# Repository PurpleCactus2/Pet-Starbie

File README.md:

# Starbie
A motion controlled PCB pet!

### Introduction
This is Starbie, a motion controlled, Tamagotchi style digital pet meant to keep you company on your desk. It uses a microcontroller, motion and enviroment sensor, along with 2 buttons to allow you to interact with it. It was made with the help of this wonderful [guide](https://github.com/SharKingStudios/Starbie/tree/main) by Logan Peterson which guided me through the entire process of making my first PCB.

Its main functions include:
- A stats screen for your pet
- Nap, Play and Pet actions
- A shake interaction

And you can also customise your own sprite!

However, I have also added a couple of my own features:
- A basic power LED indicating when starbie is on
- An external battery circuit making starbie portable
- A 3D printed enclosure to tie everything together

### PCB and Schematic
This is the entire schematic using the connections and components that are described in the guide.
The ESP32-C3 connects the buttons through 2 GPIO pins, the screen and the motion sensor through I2C, and also supplies the steady 3.3V that the circuit needs.

<br>
<br>
Here are the 2 things that I added:
<br>
<br>
This is the basic power LED which connects to the 3.3V output of the ESP32-C3 through a 220Ω resistor. The LED itself will just be a standard 5mm 2V red LED that indicates whenever the circuit is connected to power.
<br>

<br>
<br>
This is the external battery circuit that will power starbie through a battery. It will use a 500mAh 3.7V 503035 liPo that connects straight to the battery pads on the underside of the Xiao, meaning it will be charged and regulated with the battery charger already integrated into the microcontroller. A switch has also been included in line from the battery so that starbie can be turned off easily.
<br>

<br>
<br>
PCB:
<br>
<br>
Here, I have used a similar layout and shape as shown in the guide. <br> <br>
At first, I tried experimenting with the positioning of the buttons by having them side by side, but this turned out to make to routing more complicated by requiring more traces on the bottom layer. Because of this, I decided to align the buttons vertically, even if it is a little more inconvenient. I have also added a couple of M3 screw holes on the edges so that I can mount the PCB in the enclosure that I designed.

<br>
<br>
Here are the contacts for the battery pads of the Xiao:

These pads won't actually be making contact with the pads on the Xiao, since it will be raised on top of header pins. But, I have put through-holes on these pads to allow for header pins to be pushed through them. This should allow the battery to be soldered directly to these pins from the bottom, making managing space a lot easier.

### Code
Most of the code is from the preset given by the guide, but there are some parts which I have modified:
<br>
<br>
These 2 pins were previously mismatched with SCL on 7 and SDA on 6 while my PCB and schematic has SCL on 6 and SDA on 7. This would have thrown an error where the Xiao would not be able to communicate with the screen or motion sensor. Luckily the ESP32-C3 is able to reroute these I2C connections easily.
~~~cpp
const int I2C_SDA_PIN = 7;
const int I2C_SCL_PIN = 6;
~~~
<br>
<br>
This was an optional function given in the guide that could be inserted above the drawHeart function. It will create sparkles behind the pet as it moves.

~~~cpp
void drawSparkle(int x, int y) {
  display.drawPixel(x, y - 2, SSD1306_WHITE);
  display.drawPixel(x - 1, y - 1, SSD1306_WHITE);
  display.drawPixel(x + 1, y - 1, SSD1306_WHITE);
  display.drawPixel(x - 2, y, SSD1306_WHITE);
  display.drawPixel(x, y, SSD1306_WHITE);
  display.drawPixel(x + 2, y, SSD1306_WHITE);
  display.drawPixel(x - 1, y + 1, SSD1306_WHITE);
  display.drawPixel(x + 1, y + 1, SSD1306_WHITE);
  display.drawPixel(x, y + 2, SSD1306_WHITE);
}
~~~

This is what actually calls the drawSparkle function
~~~cpp
if (!isNapping() && (now / 250) % 2 == 0) {
  drawSparkle(petX - 4, petY + 18);
}
~~~
<br>
<br>
This is a byte list created from a custom 32x32px sprite which I drew.

~~~cpp
const uint8_t PROGMEM PET_SPRITE[] = {
  0x00, 0x0f, 0xf0, 0x00, 0x00, 0x70, 0x0e, 0x00, 0x01, 0x80, 0x01, 0x80, 0x02, 0x00, 0x00, 0x40, 
	0x04, 0x00, 0x00, 0x20, 0x08, 0x00, 0x00, 0x10, 0x10, 0x00, 0x00, 0x08, 0x20, 0x00, 0x38, 0x04, 
	0x20, 0x00, 0x38, 0x04, 0x40, 0x00, 0x30, 0x02, 0x40, 0x00, 0x00, 0x02, 0x40, 0x00, 0x00, 0x02, 
	0x80, 0x00, 0x00, 0x3c, 0x80, 0x00, 0x03, 0xe0, 0x80, 0x00, 0x1e, 0x00, 0x80, 0x00, 0x20, 0x00, 
	0x80, 0x00, 0x20, 0x00, 0x80, 0x00, 0x1e, 0x00, 0x80, 0x00, 0x03, 0xe0, 0x80, 0x00, 0x00, 0x3c, 
	0x40, 0x00, 0x00, 0x02, 0x40, 0x00, 0x00, 0x02, 0x40, 0x00, 0x00, 0x02, 0x20, 0x00, 0x00, 0x04, 
	0x20, 0x00, 0x00, 0x04, 0x10, 0x00, 0x00, 0x08, 0x08, 0x00, 0x00, 0x10, 0x04, 0x00, 0x00, 0x20, 
	0x02, 0x00, 0x00, 0x40, 0x01, 0x80, 0x01, 0x80, 0x00, 0x70, 0x0e, 0x00, 0x00, 0x0f, 0xf0, 0x00,
};
~~~

The sprite should look like this:

### Enclosure
I wanted to make the PCB a little more personalised and I also wanted to have a neat place to store the battery. Because of this, I decided to design a 3D printable enclosure meant to be assembled with screws and a little bit of glue.

This is the enclosure as a whole. It has several holes on the top for each component that sticks through, along with 4 M2.5x8 screw holes along the edge of the lid for assembly.

<br>
<br>
<br>
This is how the battery and the switch are arranged below the PCB. The battery is completely hidden inside the bottom of the case while the switch sticks out a little bit through a hole so that you can use it.

<br>
<br>
<br>
This is how the entire enclosure is assembled. The battery and the PCB are inserted into the case first, along with 4 M3x8 that screw into holes in the bottom of the case. The lid is then put on with 4 M2.5x8 along its edges. Finally after trimming the pins of the switch, it is super-glued onto the back of the PCB next to the battery.

<br>
<br>
<br>
Here is a more detailed view of the screw holes inside the case as well as of the battery and switch placement:

### BOM
| Part | What it's for | Qty | Unit | Total | Vendor | Expected Discounted Price (At time last checked) |
| --- | --- | --- | --- | --- | --- | --- |
| [XIAO ESP32 C3](https://www.aliexpress.com/item/1005008791937363.html?spm=a2g0o.productlist.main.57.73cf3205oRycWV&algo_pvid=b26d9f0b-0926-4227-8f6e-a914df534036&algo_exp_id=b26d9f0b-0926-4227-8f6e-a914df534036-54&pdp_ext_f=%7B%22order%22%3A%221488%22%2C%22spu_best_type%22%3A%22price%22%2C%22eval%22%3A%221%22%2C%22fromPage%22%3A%22search%22%7D&pdp_npi=6%40dis%21NOK%2183.14%2110.88%21%21%218.33%211.09%21%402103810f17916626052361400e0f0b%2112000052930246748%21sea%21NO%218463637778%21X%211%210%21n_tag%3A-29911%3Bd%3A22d43e35%3Bm03_new_user%3A-29895%3BpisId%3A5000000219435413&curPageLogUid=9fTnC7rBXexc&utparam-url=scene%3Asearch%7Cquery_from%3A%7Cx_object_id%3A1005008791937363%7C_p_origin_prod%3A) | The main microcontroller | 1 | $8.84 | $8.84 | [AliExpress](https://www.aliexpress.com/item/1005008791937363.html?spm=a2g0o.productlist.main.57.73cf3205oRycWV&algo_pvid=b26d9f0b-0926-4227-8f6e-a914df534036&algo_exp_id=b26d9f0b-0926-4227-8f6e-a914df534036-54&pdp_ext_f=%7B%22order%22%3A%221488%22%2C%22spu_best_type%22%3A%22price%22%2C%22eval%22%3A%221%22%2C%22fromPage%22%3A%22search%22%7D&pdp_npi=6%40dis%21NOK%2183.14%2110.88%21%21%218.33%211.09%21%402103810f17916626052361400e0f0b%2112000052930246748%21sea%21NO%218463637778%21X%211%210%21n_tag%3A-29911%3Bd%3A22d43e35%3Bm03_new_user%3A-29895%3BpisId%3A5000000219435413&curPageLogUid=9fTnC7rBXexc&utparam-url=scene%3Asearch%7Cquery_from%3A%7Cx_object_id%3A1005008791937363%7C_p_origin_prod%3A) | $2.46 |
| [0.96" OLED](https://www.aliexpress.com/item/1005006141235306.html?spm=a2g0o.productlist.main.1.4f9d12780KL1MO&algo_pvid=39c5fa34-e376-41e0-8849-d3f33eab2a7b&algo_exp_id=39c5fa34-e376-41e0-8849-d3f33eab2a7b-0&pdp_ext_f=%7B%22order%22%3A%2226478%22%2C%22spu_best_type%22%3A%22price%22%2C%22eval%22%3A%221%22%2C%22fromPage%22%3A%22search%22%7D&pdp_npi=6%40dis%21NOK%2122.70%2122.70%21%21%2115.22%2115.22%21%400b5e1a3817916636389462446e0d42%2112000035944225406%21sea%21NO%218463637778%21X%211%210%21n_tag%3A-29911%3Bd%3A22d43e35%3Bm03_new_user%3A-29895&curPageLogUid=3zuT5PcCui5q&utparam-url=scene%3Asearch%7Cquery_from%3A%7Cx_object_id%3A1005006141235306%7C_p_origin_prod%3A) | For displaying the sprite and actions | 1 | $2.31 | $2.31 | [AliExpress](https://www.aliexpress.com/item/1005006141235306.html?spm=a2g0o.productlist.main.1.4f9d12780KL1MO&algo_pvid=39c5fa34-e376-41e0-8849-d3f33eab2a7b&algo_exp_id=39c5fa34-e376-41e0-8849-d3f33eab2a7b-0&pdp_ext_f=%7B%22order%22%3A%2226478%22%2C%22spu_best_type%22%3A%22price%22%2C%22eval%22%3A%221%22%2C%22fromPage%22%3A%22search%22%7D&pdp_npi=6%40dis%21NOK%2122.70%2122.70%21%21%2115.22%2115.22%21%400b5e1a3817916636389462446e0d42%2112000035944225406%21sea%21NO%218463637778%21X%211%210%21n_tag%3A-29911%3Bd%3A22d43e35%3Bm03_new_user%3A-29895&curPageLogUid=3zuT5PcCui5q&utparam-url=scene%3Asearch%7Cquery_from%3A%7Cx_object_id%3A1005006141235306%7C_p_origin_prod%3A) | — |
| [MPU6050](https://www.aliexpress.com/item/1005010602044047.html?spm=a2g0o.productlist.main.1.48303357RDfjHx&algo_pvid=4210383c-c501-405f-a9e2-f9a703648051&algo_exp_id=4210383c-c501-405f-a9e2-f9a703648051-0&pdp_ext_f=%7B%22order%22%3A%22788%22%2C%22eval%22%3A%221%22%2C%22fromPage%22%3A%22search%22%7D&pdp_npi=6%40dis%21NOK%2120.03%2120.03%21%21%2113.43%2113.43%21%40210384a717916639655816378e0e45%2112000052945138544%21sea%21NO%218463637778%21X%211%210%21n_tag%3A-29911%3Bd%3A22d43e35%3Bm03_new_user%3A-29895&curPageLogUid=bgBBlxWptc6U&utparam-url=scene%3Asearch%7Cquery_from%3A%7Cx_object_id%3A1005010602044047%7C_p_origin_prod%3A) | For calculating  orientation and acceleration | 1 | $2.10 | $2.10 | [AliExpress](https://www.aliexpress.com/item/1005010602044047.html?spm=a2g0o.productlist.main.1.48303357RDfjHx&algo_pvid=4210383c-c501-405f-a9e2-f9a703648051&algo_exp_id=4210383c-c501-405f-a9e2-f9a703648051-0&pdp_ext_f=%7B%22order%22%3A%22788%22%2C%22eval%22%3A%221%22%2C%22fromPage%22%3A%22search%22%7D&pdp_npi=6%40dis%21NOK%2120.03%2120.03%21%21%2113.43%2113.43%21%40210384a717916639655816378e0e45%2112000052945138544%21sea%21NO%218463637778%21X%211%210%21n_tag%3A-29911%3Bd%3A22d43e35%3Bm03_new_user%3A-29895&curPageLogUid=bgBBlxWptc6U&utparam-url=scene%3Asearch%7Cquery_from%3A%7Cx_object_id%3A1005010602044047%7C_p_origin_prod%3A) | — |
| [DHT11](https://www.aliexpress.com/item/1005007728845619.html?spm=a2g0o.productlist.main.37.478071f3CCmwdm&algo_pvid=8a062715-841e-4e9b-bf6d-60feb66e7b31&algo_exp_id=8a062715-841e-4e9b-bf6d-60feb66e7b31-36&pdp_ext_f=%7B%22order%22%3A%222170%22%2C%22spu_best_type%22%3A%22price%22%2C%22eval%22%3A%221%22%2C%22fromPage%22%3A%22search%22%7D&pdp_npi=6%40dis%21NOK%2125.07%2116.96%21%21%2116.81%2111.37%21%4021038db317916647905926102e0fe8%2112000042055448713%21sea%21NO%218463637778%21X%211%210%21n_tag%3A-29911%3Bd%3A22d43e35%3Bm03_new_user%3A-29895&curPageLogUid=2wPSphHKUwT4&utparam-url=scene%3Asearch%7Cquery_from%3A%7Cx_object_id%3A1005007728845619%7C_p_origin_prod%3A) | For measuring temperature and humidity (Just the bare module, no breakout board) | 1 | $2.80 | $2.80 | [AliExpress](https://www.aliexpress.com/item/1005007728845619.html?spm=a2g0o.productlist.main.37.478071f3CCmwdm&algo_pvid=8a062715-841e-4e9b-bf6d-60feb66e7b31&algo_exp_id=8a062715-841e-4e9b-bf6d-60feb66e7b31-36&pdp_ext_f=%7B%22order%22%3A%222170%22%2C%22spu_best_type%22%3A%22price%22%2C%22eval%22%3A%221%22%2C%22fromPage%22%3A%22search%22%7D&pdp_npi=6%40dis%21NOK%2125.07%2116.96%21%21%2116.81%2111.37%21%4021038db317916647905926102e0fe8%2112000042055448713%21sea%21NO%218463637778%21X%211%210%21n_tag%3A-29911%3Bd%3A22d43e35%3Bm03_new_user%3A-29895&curPageLogUid=2wPSphHKUwT4&utparam-url=scene%3Asearch%7Cquery_from%3A%7Cx_object_id%3A1005007728845619%7C_p_origin_prod%3A) | $1.89 |
| [MX Switches](https://www.aliexpress.com/item/1005006376024657.html?spm=a2g0o.productlist.main.1.165735f5ClXEcQ&algo_pvid=4a830536-a4b2-499f-a21c-93d9edf09368&algo_exp_id=4a830536-a4b2-499f-a21c-93d9edf09368-0&pdp_ext_f=%7B%22order%22%3A%222317%22%2C%22eval%22%3A%221%22%2C%22fromPage%22%3A%22search%22%7D&pdp_npi=6%40dis%21NOK%2137.52%2110.88%21%21%2125.16%217.30%21%400b0fe40d17916655923207967e1029%2112000037159110206%21sea%21NO%218463637778%21X%211%210%21n_tag%3A-29911%3Bd%3A22d43e35%3Bm03_new_user%3A-29895%3BpisId%3A5000000219435413&curPageLogUid=OjmnomvXuXFE&utparam-url=scene%3Asearch%7Cquery_from%3A%7Cx_object_id%3A1005006376024657%7C_p_origin_prod%3A) | Buttons to control different functions (Minimum order size: 10pcs) | 1 | $3.93 | $3.93 | [AliExpress](https://www.aliexpress.com/item/1005006376024657.html?spm=a2g0o.productlist.main.1.165735f5ClXEcQ&algo_pvid=4a830536-a4b2-499f-a21c-93d9edf09368&algo_exp_id=4a830536-a4b2-499f-a21c-93d9edf09368-0&pdp_ext_f=%7B%22order%22%3A%222317%22%2C%22eval%22%3A%221%22%2C%22fromPage%22%3A%22search%22%7D&pdp_npi=6%40dis%21NOK%2137.52%2110.88%21%21%2125.16%217.30%21%400b0fe40d17916655923207967e1029%2112000037159110206%21sea%21NO%218463637778%21X%211%210%21n_tag%3A-29911%3Bd%3A22d43e35%3Bm03_new_user%3A-29895%3BpisId%3A5000000219435413&curPageLogUid=OjmnomvXuXFE&utparam-url=scene%3Asearch%7Cquery_from%3A%7Cx_object_id%3A1005006376024657%7C_p_origin_prod%3A) | $1.14 |
| [PCB](https://cart.jlcpcb.com/quote?spm=jlcpcb.Public.2006&spm=Jlcpcb.Instantquote&_t=1791669462672&up_spm=Jlcpcb.Loginpage.1003) | Main Board (Use gerbers provided) | 1 | $4.00 | $4.00 | [JLCPCB](https://cart.jlcpcb.com/quote?spm=jlcpcb.Public.2006&spm=Jlcpcb.Instantquote&_t=1791669462672&up_spm=Jlcpcb.Loginpage.1003) | — |
| [3.7V Battery](https://www.aliexpress.com/item/1005009736068698.html?spm=a2g0o.productlist.main.4.459d833dURhCco&aem_p4p_detail=2026101112294712192696271259420002832870&algo_pvid=ee05ab26-0bdd-40f0-89cd-5b4f3bde79ca&algo_exp_id=ee05ab26-0bdd-40f0-89cd-5b4f3bde79ca-3&pdp_ext_f=%7B%22order%22%3A%22411%22%2C%22eval%22%3A%221%22%2C%22fromPage%22%3A%22search%22%7D&pdp_npi=6%40dis%21NOK%21189.77%2134.99%21%21%21127.26%2123.47%21%4021038c6f17917469876191933e0f30%2112000049991282150%21sea%21NO%218463637778%21X%211%210%21n_tag%3A-29911%3Bd%3A22d43e35%3Bm03_new_user%3A-29895%3BpisId%3A5000000219435413&curPageLogUid=E1q33SLX1xs4&utparam-url=scene%3Asearch%7Cquery_from%3A%7Cx_object_id%3A1005009736068698%7C_p_origin_prod%3A&search_p4p_id=2026101112294712192696271259420002832870_1) | Powering the device while not connected (**Can be self funded**) | 1 | $0.01 | $0.01 | [AliExpress](https://www.aliexpress.com/item/1005009736068698.html?spm=a2g0o.productlist.main.4.459d833dURhCco&aem_p4p_detail=2026101112294712192696271259420002832870&algo_pvid=ee05ab26-0bdd-40f0-89cd-5b4f3bde79ca&algo_exp_id=ee05ab26-0bdd-40f0-89cd-5b4f3bde79ca-3&pdp_ext_f=%7B%22order%22%3A%22411%22%2C%22eval%22%3A%221%22%2C%22fromPage%22%3A%22search%22%7D&pdp_npi=6%40dis%21NOK%21189.77%2134.99%21%21%21127.26%2123.47%21%4021038c6f17917469876191933e0f30%2112000049991282150%21sea%21NO%218463637778%21X%211%210%21n_tag%3A-29911%3Bd%3A22d43e35%3Bm03_new_user%3A-29895%3BpisId%3A5000000219435413&curPageLogUid=E1q33SLX1xs4&utparam-url=scene%3Asearch%7Cquery_from%3A%7Cx_object_id%3A1005009736068698%7C_p_origin_prod%3A&search_p4p_id=2026101112294712192696271259420002832870_1) | $3.66 |
| [Passive Components](https://www.aliexpress.com/item/1005002489867848.html?spm=a2g0o.productlist.main.9.370926a8ctSQGM&algo_pvid=7c869774-9e38-45cb-95e6-598a8294238c&algo_exp_id=7c869774-9e38-45cb-95e6-598a8294238c-8&pdp_ext_f=%7B%22order%22%3A%225679%22%2C%22eval%22%3A%221%22%2C%22fromPage%22%3A%22search%22%7D&pdp_npi=6%40dis%21NOK%215.69%215.69%21%21%210.57%210.57%21%402103842a17917251852512610e0d09%2112000020846080146%21sea%21NO%218463637778%21X%211%210%21n_tag%3A-29911%3Bd%3A22d43e35%3Bm03_new_user%3A-29895&curPageLogUid=x1GYFxVaUCZz&utparam-url=scene%3Asearch%7Cquery_from%3A%7Cx_object_id%3A1005002489867848%7C_p_origin_prod%3A) | (Resistors, LED, Switch) (**Self provided**) | 1 | $0.01 | $0.01 | (Example part) [AliExpress](https://www.aliexpress.com/item/1005002489867848.html?spm=a2g0o.productlist.main.9.370926a8ctSQGM&algo_pvid=7c869774-9e38-45cb-95e6-598a8294238c&algo_exp_id=7c869774-9e38-45cb-95e6-598a8294238c-8&pdp_ext_f=%7B%22order%22%3A%225679%22%2C%22eval%22%3A%221%22%2C%22fromPage%22%3A%22search%22%7D&pdp_npi=6%40dis%21NOK%215.69%215.69%21%21%210.57%210.57%21%402103842a17917251852512610e0d09%2112000020846080146%21sea%21NO%218463637778%21X%211%210%21n_tag%3A-29911%3Bd%3A22d43e35%3Bm03_new_user%3A-29895&curPageLogUid=x1GYFxVaUCZz&utparam-url=scene%3Asearch%7Cquery_from%3A%7Cx_object_id%3A1005002489867848%7C_p_origin_prod%3A) | — |
| [Screws](https://www.aliexpress.com/item/33043885403.html?spm=a2g0o.productlist.main.1.704136c54twNW7&algo_pvid=0f932d31-3b09-495f-9419-6458a1488934&algo_exp_id=0f932d31-3b09-495f-9419-6458a1488934-0&pdp_ext_f=%7B%22order%22%3A%2214327%22%2C%22spu_best_type%22%3A%22price%22%2C%22eval%22%3A%221%22%2C%22fromPage%22%3A%22search%22%7D&pdp_npi=6%40dis%21NOK%2116.97%2116.97%21%21%211.70%211.70%21%400b1585c117917410156522141e0dd5%2112000020018123413%21sea%21NO%218463637778%21X%211%210%21n_tag%3A-29911%3Bd%3A22d43e35%3Bm03_new_user%3A-29895&curPageLogUid=5T3k97JHejJu&utparam-url=scene%3Asearch%7Cquery_from%3A%7Cx_object_id%3A33043885403%7C_p_origin_prod%3A) | For assembly of the enclosure, 4x self-tapping M3x8  and M2.5x8 (**Self provided**) | 1 | $0.01 | $0.01 | (Example part) [AliExpress](https://www.aliexpress.com/item/33043885403.html?spm=a2g0o.productlist.main.1.704136c54twNW7&algo_pvid=0f932d31-3b09-495f-9419-6458a1488934&algo_exp_id=0f932d31-3b09-495f-9419-6458a1488934-0&pdp_ext_f=%7B%22order%22%3A%2214327%22%2C%22spu_best_type%22%3A%22price%22%2C%22eval%22%3A%221%22%2C%22fromPage%22%3A%22search%22%7D&pdp_npi=6%40dis%21NOK%2116.97%2116.97%21%21%211.70%211.70%21%400b1585c117917410156522141e0dd5%2112000020018123413%21sea%21NO%218463637778%21X%211%210%21n_tag%3A-29911%3Bd%3A22d43e35%3Bm03_new_user%3A-29895&curPageLogUid=5T3k97JHejJu&utparam-url=scene%3Asearch%7Cquery_from%3A%7Cx_object_id%3A33043885403%7C_p_origin_prod%3A) | — |
| **Parts subtotal** | — | — | — | **$24.01** | — | **$17.56** |
| **Tax & shipping** | — | — | — | **$6.97** | — | **$7.87** |
| **Total** | — | — | — | **$30.98** | — | **$25.43** |

**Please Note:** 
- For full transparency only the raw prices for each component have been listed, in reality significant discounts do apply for almost all of the components. **The total of $30.98 represents the maximum possible price** for all the components, discounted prices are shown in the right column and in cart screenshots below
- Shipping has been disregarded for all components except for the PCB because of the free shipping offer applied to all choice orders above 10$
- The "first order discount" has been included in the price of the PCB, being taken away from the shipping cost (ie. 4$ PCB + 8.16$ shipping --> 4$ PCB + 4.16$ shipping), this has been done so that the project can still be submitted in the 30$ tier
- The keycaps for the switches and the enclosure will be 3D-printed so no listing has been provided
- I am willing to fund/provide all other components which do not fit into the 30$ range myself (Passive components that I already have, battery, and any other additional shipping and tax that may apply)

Cart Screenshots:

AliExpress Order (Excluding Self-funded parts) (1kr ≈ $0.1):

Final payment window including tax:

(129.24kr = **$13.52**)
<br>
<br>
<br>
Self-Funded part order (If the previous discounts are considered valid and are still availiable, then the extra money could still be used for this): 

Final payment window including tax:

(42.86kr = **$4.48**)
<br>
<br>
<br>
JLCPCB Order:

<br>
<br>
<br>
Grand Total (with discounts at time last checked): <b>$25.43<b>

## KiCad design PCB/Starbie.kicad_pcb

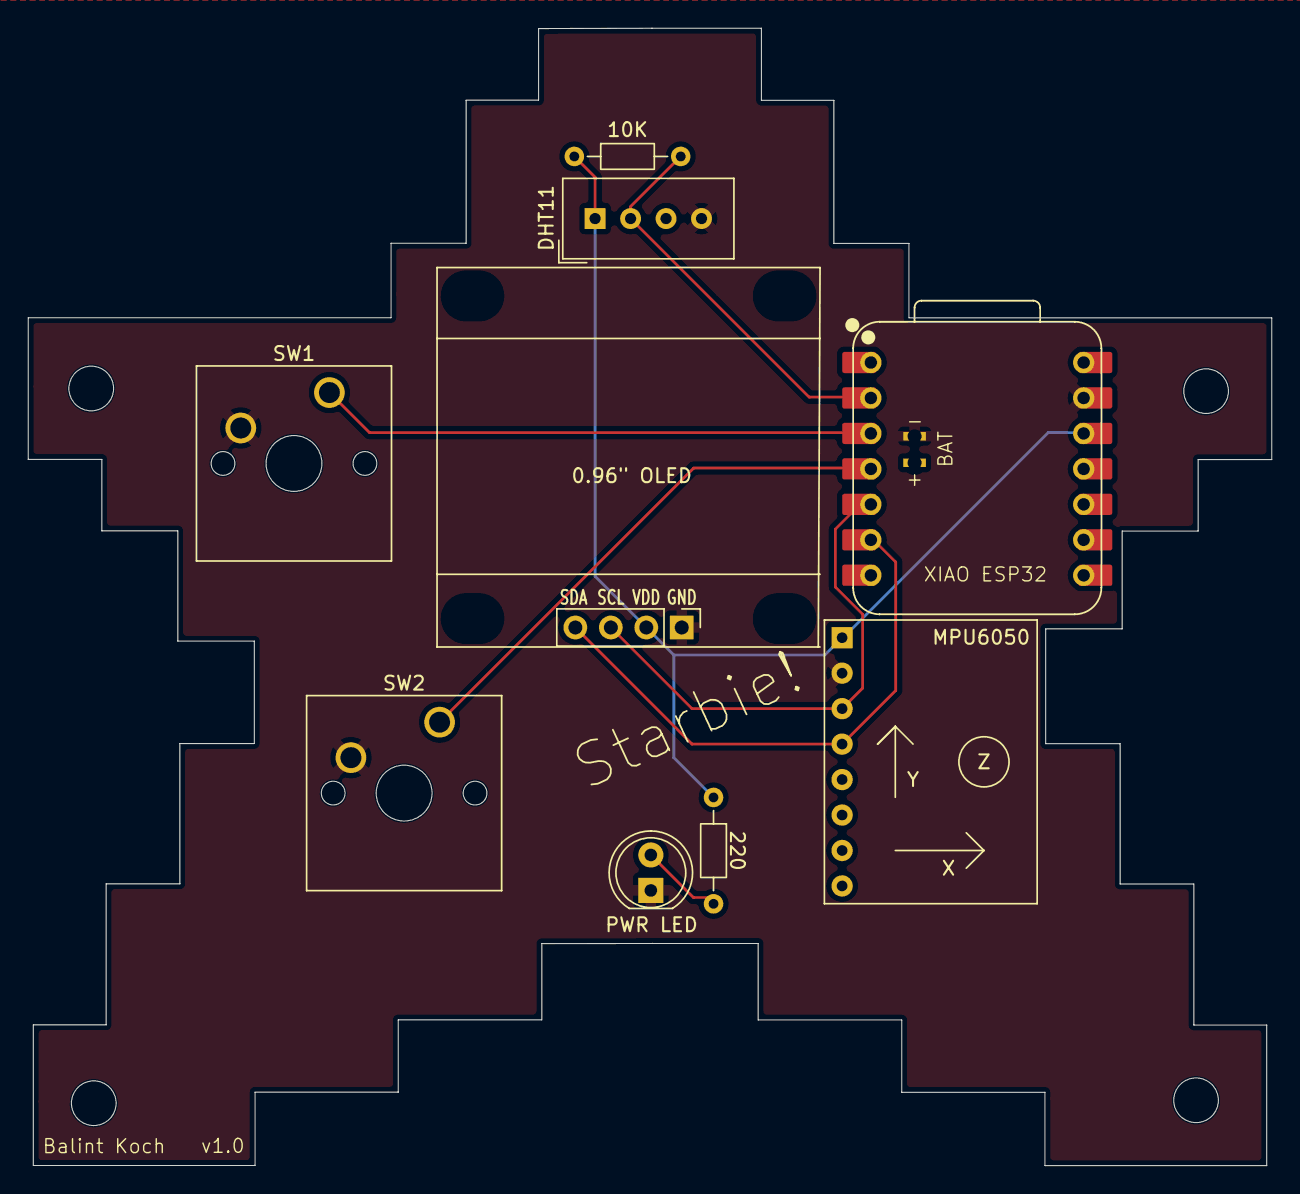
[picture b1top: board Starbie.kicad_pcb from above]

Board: 2 copper layers, 89.1 x 81.5 mm, 10 parts (0 on the bottom side), 8 nets.

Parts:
0.96" OLED: OLED; Display_128x64_096_I2C
10K: 10K; R_Axial_DIN0204_L3.6mm_D1.6mm_P7.62mm_Horizontal
220: 220; R_Axial_DIN0204_L3.6mm_D1.6mm_P7.62mm_Horizontal
DHT11: DHT11; Aosong_DHT11_5.5x12.0_P2.54mm
J3: Battery Pads; XIAO-ESP32-BATTCONTACTS
MPU6050: MPU6050; MPU6050_Module
PWR LED: LED; LED_D5.0mm
SW1, SW2: SW_Push; SW_Cherry_MX_1.00u_PCB
U1: XIAO-ESP32-C3-SMD; XIAO-ESP32-C6-DIP

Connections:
+3.3V: 0.96" OLED.2, 10K.1, 220.1, DHT11.1 (VDD), MPU6050.1, U1.12 (3V3_OUT)
/DHT11 DATA: 10K.2, DHT11.2 (DATA), U1.2 (D1)
/GPIO 2: SW1.1, U1.3 (D2)
/GPIO 3: SW2.1, U1.4 (D3)
/PWR LED: 220.2, PWR LED.2 (A)
/SCL: 0.96" OLED.3, MPU6050.3, U1.5 (D4)
/SDA: 0.96" OLED.4, MPU6050.4, U1.6 (D5)
GND: 0.96" OLED.1, DHT11.4 (GND), J3.-, MPU6050.2, PWR LED.1 (K), SW1.2, SW2.2, U1.13 (GND)
